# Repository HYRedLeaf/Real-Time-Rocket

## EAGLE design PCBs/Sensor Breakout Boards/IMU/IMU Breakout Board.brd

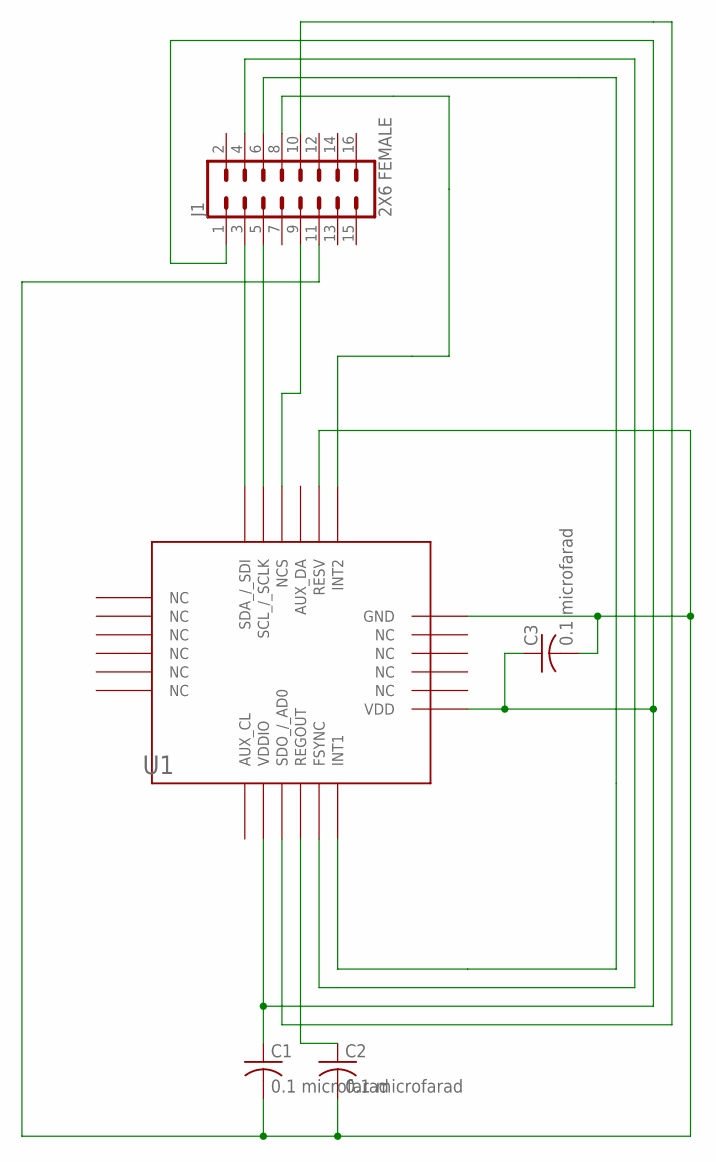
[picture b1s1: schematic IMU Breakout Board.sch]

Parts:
C1, C2, C3: 0.1 microfarad; C1206
J1: 2X6 FEMALE; 2X7
U1: ICM_20649; ICM-20649

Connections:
GND: C1.2, C2.2, C3.2, J1.11, U1.P7 (RESV), U1.P23 (GND)
unnamed: J1.4, U1.P4 (FSYNC)
unnamed: J1.6, U1.P5 (INT1)
unnamed: J1.8, U1.P6 (INT2)
unnamed: J1.9, U1.P9 (NCS)
unnamed: J1.3, U1.P11 (SDA_/_SDI)
unnamed: J1.5, U1.P10 (SCL_/_SCLK)
unnamed: J1.10, U1.P2 (SDO_/_AD0)
unnamed: C1.1, C3.1, J1.1, U1.P1 (VDDIO), U1.P18 (VDD)
unnamed: C2.1, U1.P3 (REGOUT)

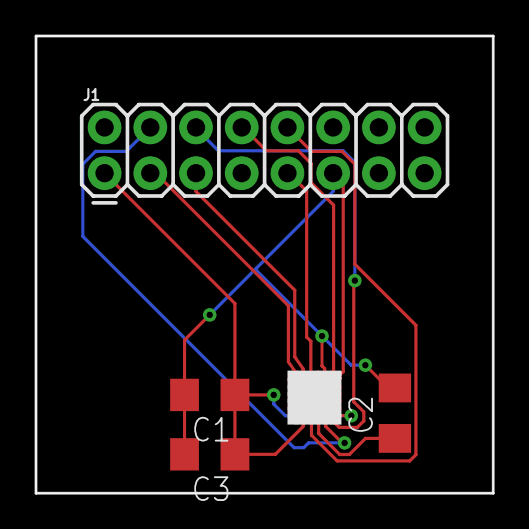
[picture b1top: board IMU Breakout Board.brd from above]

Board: 2 copper layers, 25.4 x 25.4 mm, 5 parts (0 on the bottom side), 10 nets.

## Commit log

2019-10-26 Copy over Anyssa's work
2019-11-07 IMU breakout board rev 1 complete
2019-11-07 rev 2 imu board complete
2019-11-07 Small tweaks to IMU board
2019-11-09 Reshuffled decoupling capacitors on IMU board
2020-10-11 Added ground planes
